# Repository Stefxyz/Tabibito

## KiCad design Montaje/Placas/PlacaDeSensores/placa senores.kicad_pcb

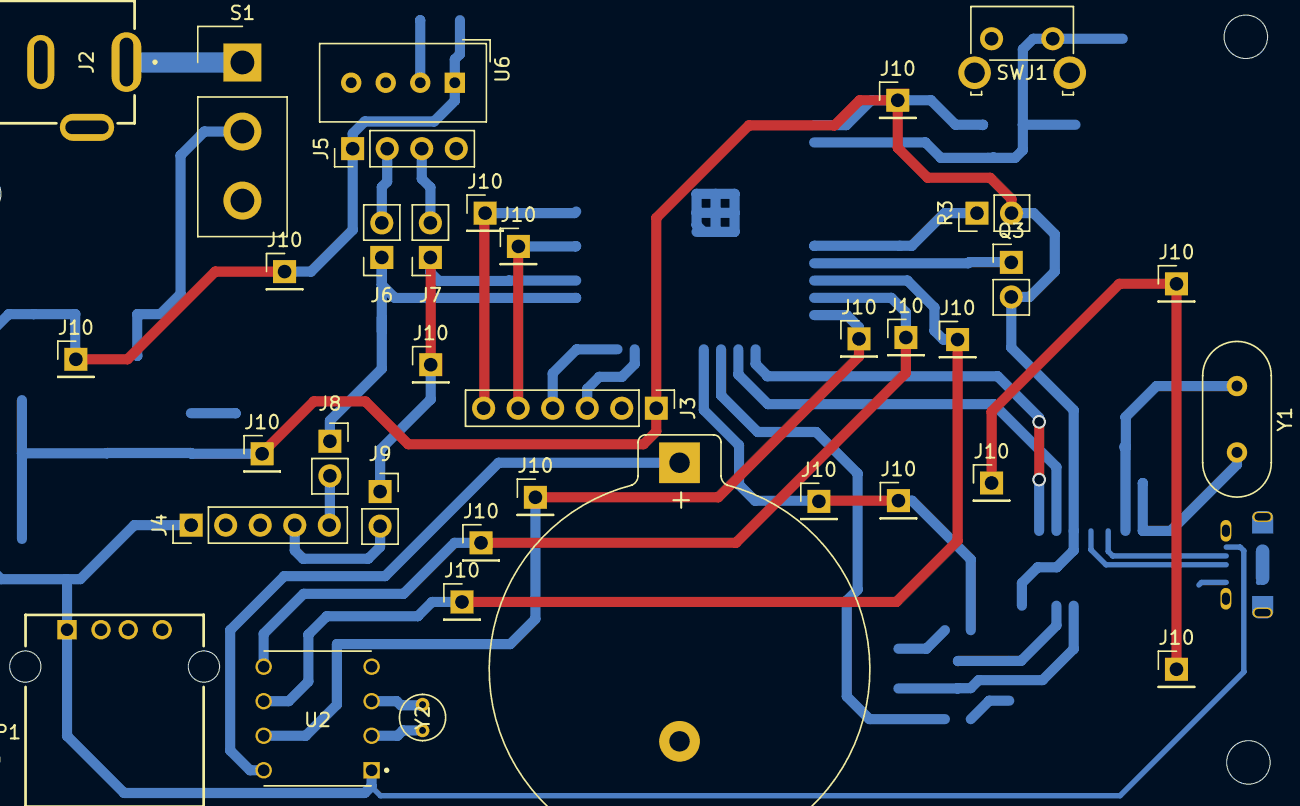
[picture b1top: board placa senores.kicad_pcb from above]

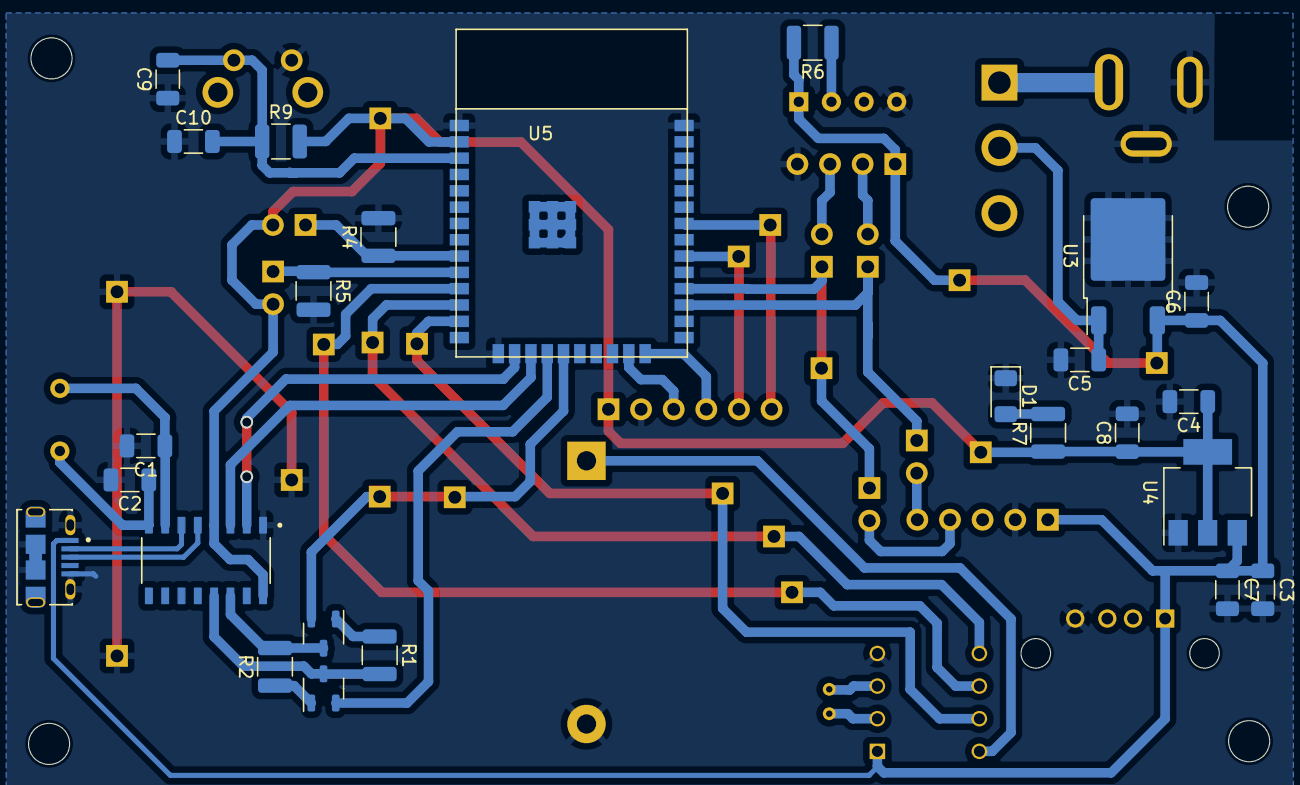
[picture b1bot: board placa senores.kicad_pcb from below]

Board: 2 copper layers, 65 parts (25 on the bottom side), 39 nets.

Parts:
BT1: Pila; BatteryHolder_Keystone_105_1x2430
C1, C2: 22n; C_1206_3216Metric
C3: 0,1uF; C_1206_3216Metric
C4: 10uF; C_1206_3216Metric
C5, C6, C7, C8: 10u; C_1206_3216Metric
C9, C10: 0.1u; C_1206_3216Metric
D1: LED; LED_1206_3216Metric
H1, H2, H3, H4: MountingHole; MountingHole_3.2mm_M3
J1: 10118194-0001LF; AMPHENOL_10118194-0001LF
J2: DCJ200-10-A-XX-K_REVA; GCT_DCJ200-10-A-XX-K_REVA
J3: bmp280; PinHeader_1x06_P2.54mm_Vertical
J4: Screw_Terminal_01x05; PinHeader_1x05_P2.54mm_Vertical
J5: Screw_Terminal_01x04; PinHeader_1x04_P2.54mm_Vertical
J6, J7, J8, J9: Screw_Terminal_01x02; PinSocket_1x02_P2.54mm_Vertical
J10, J10#2, J10#3, J10#4, J10#5, J10#6, J10#7, J10#8, J10#9, J10#10, J10#11, J10#12, J10#13, J10#14, J10#15, J10#16, J10#17, J10#18: Screw_Terminal_01x01; PinHeader_1x01_P2.54mm_Vertical
P1: USB-A1HSW6; OST_USB-A1HSW6
Q1, Q2: BC847; SOT-23-3
Q3: Fototransistor; PinHeader_1x02_P2.54mm_Vertical
R1, R2: 10k; R_1210_3225Metric
R3: LDR07; PinHeader_1x02_P2.54mm_Vertical
R4: 5,6K; R_1210_3225Metric
R5: 1M; R_1210_3225Metric
R6: 4,7K; R_1210_3225Metric
R7: 330; R_1210_3225Metric
R9: 4.7k; R_1210_3225Metric
S1: RB141C1100; Samtec_HPM-03-05-x-S_Straight_1x03_Pitch5.08mm
SWJ1: SW_MEC_5G; SW_SPST_Omron_B3F-315x_Angled
U1: CH340G; SOIC127P600X180-16N
U2: DS1302; DIP794W47P254L991H457Q8
U3: KA78M05_TO252; TO-252-2
U4: AMS1117; SOT-223-3_TabPin2
U5: ESP32-WROOM-32E
U6: DHT11; Aosong_DHT11_5.5x12.0_P2.54mm
Y1: Crystal; Crystal_HC49-4H_Vertical
Y2: Crystal; Crystal_C38-LF_D3.0mm_L8.0mm_Vertical

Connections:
+3V3: C4.1, C8.1, J3.1, J10#6.1, J10#17.1, Q3.2 (E), R3.2, R7.1, R9.2, U1.4 (V3), U1.16 (VCC), U4.2 (VO), U5.2 (VDD)
+5V: C3.1, C6.1, C7.1, J1.1, J4.1, J5.1, J10#11.1, J10#16.1, P1.1 (VBUS), R6.2, U2.1 (VCC), U3.3 (VO), U4.3 (VI), U6.1 (VCC)
/+D: J1.3, U1.5 (UD+)
/-D: J1.2, U1.6 (UD-)
/ADC_LDR: R3.1, R4.1, U5.9 (IO33)
/ADC_PD: Q3.1 (C), R5.1, U5.10 (IO25)
/CLK: J10#2.1, J10#12.1, U2.7 (SCLK), U5.13 (IO14)
/CSB: J3.5, J10#8.1, U5.30 (IO18)
/DTR: Q2.3 (E), R1.2, U1.13 (~DTR)
/Data: J10.1, J10#7.1, U2.6 (I/O), U5.11 (IO26)
/EN: C9.2, C10.2, R9.1, SWJ1.2 (B), U5.3 (EN)
/EN 1: J10#9.1, J10#15.1, Q1.2 (C), U5.19 (NC@19)
/GPIO_DHT22: R6.1, U6.2 (IO)
/ID0: Q2.2 (C), U5.18 (NC@18)
/RESET: J10#10.1, J10#13.1, U2.5 (CE), U5.12 (IO27)
/RST: Q1.3 (E), R2.2, U1.14 (~RTS)
/RX0: J4.4, J9.2
/RX01: J5.3, J7.2
/RX pin: J7.1, J9.1, J10#5.1, U5.28 (IO17)
/Rx: U1.3 (RXD), U5.17 (NC@17)
/SCL: J3.3, U5.23 (IO15)
/SDA: J3.4, U5.24 (IO2)
/SDO: J3.6, J10#3.1, U5.32 (NC@32)
/TX0: J4.5, J8.2
/TX01: J5.2, J6.2
/TX pin: J6.1, J8.1, U5.27 (IO16)
/Tx: U1.2 (TXD), U5.16 (IO13)
/Vin: J2.1, S1.1
/Vpila: BT1.1 (+), U2.8 (VBAT)
/XI: C1.1, U1.7 (XI), Y1.1
/XO: C2.1, U1.8 (XO), Y1.2
GND: BT1.2 (-), C1.2, C2.2, C3.2, C4.2, C5.2, C6.2, C7.2, C8.2, C9.1, C10.1, D1.1 (K), J1.5, J1.S1 (SHIELD), J1.S2 (SHIELD), J1.S4 (SHIELD), J1.S5 (SHIELD), J2.2, J2.3, J3.2, J4.2, J5.4, J10#4.1, J10#14.1, J10#18.1, P1.4 (GND), R4.2, R5.2, SWJ1.1 (A), U1.1 (GND), U2.4 (GND), U3.2 (GND), U4.1 (ADJ), U5.1 (GND@1), U5.15 (GND@15), U5.38 (GND@38), U6.4 (GND)
unnamed: D1.2 (A), R7.2
unnamed: Q1.1 (B), R1.1
unnamed: Q2.1 (B), R2.1
unnamed: U2.2 (X1), Y2.2
unnamed: U2.3 (X2), Y2.1
unnamed: U5.GND@39 (THERMAL@39), U5.GND@40 (THERMAL@39), U5.GND@41 (THERMAL@39), U5.GND@42 (THERMAL@39), U5.GND@43 (THERMAL@39), U5.GND@44 (THERMAL@39), U5.GND@45 (THERMAL@39), U5.GND@46 (THERMAL@39), U5.GND@47 (THERMAL@39)
VCC: C5.1, S1.2, U3.1 (VI)

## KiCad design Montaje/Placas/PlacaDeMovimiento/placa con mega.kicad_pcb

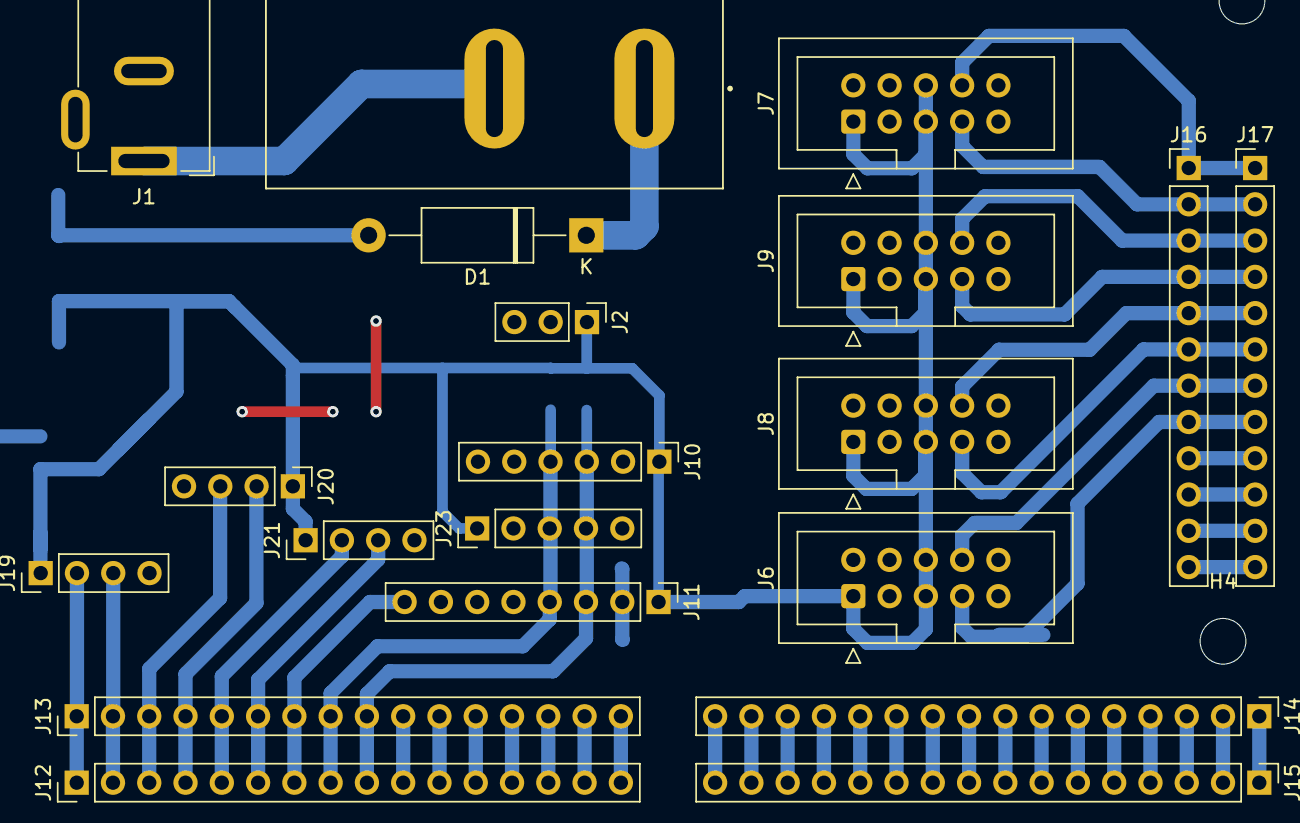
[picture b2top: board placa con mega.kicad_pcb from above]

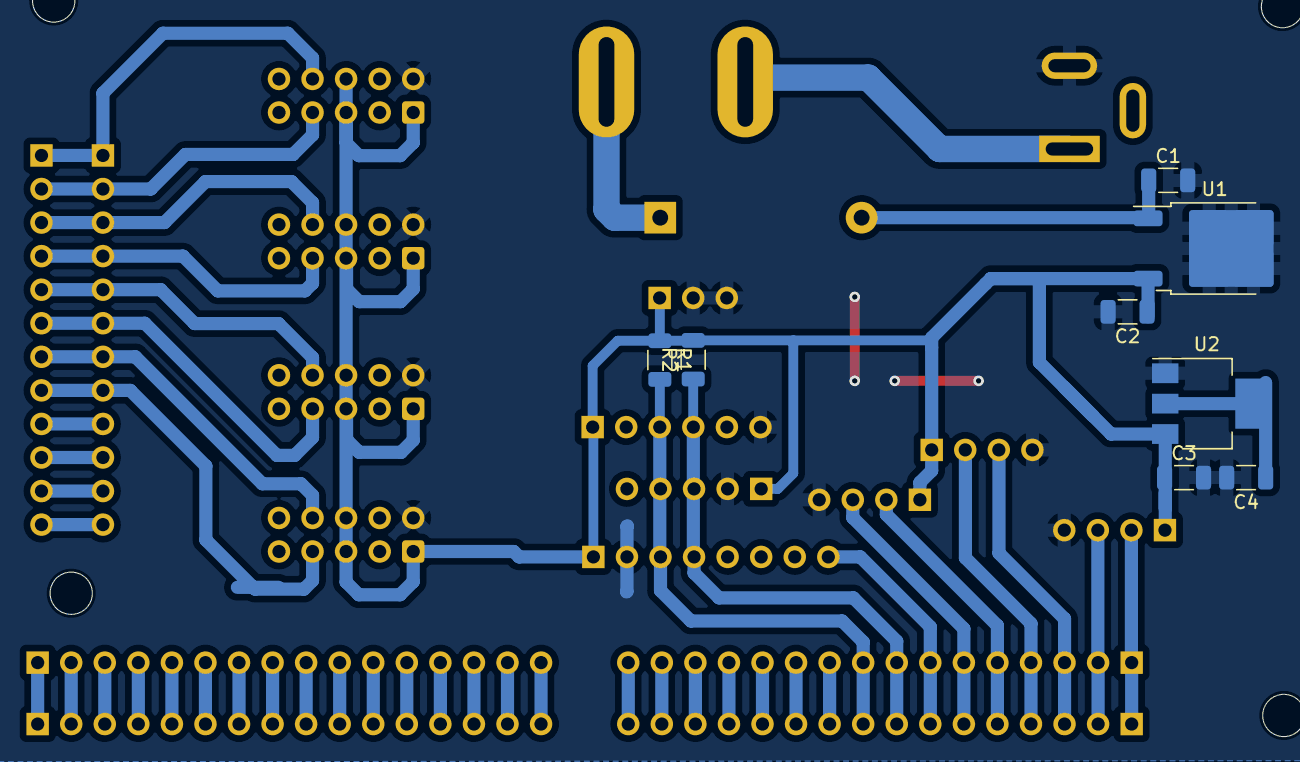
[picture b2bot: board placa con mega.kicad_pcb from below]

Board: 2 copper layers, 32 parts (8 on the bottom side), 50 nets.

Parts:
C1: 0,33uF; C_1206_3216Metric
C2: 0,1uF; C_1206_3216Metric
C3, C4: 10u; C_1206_3216Metric
D1: DIODE; D_DO-15_P15.24mm_Horizontal
H1, H2, H3, H4: MountingHole; MountingHole_3.2mm_M3
J1: Jack-DC; BarrelJack_GCT_DCJ200-10-A_Horizontal
J2: Screw_Terminal_01x03; PinHeader_1x03_P2.54mm_Vertical
J6: motor 1; IDC-Header_2x05_P2.54mm_Vertical
J7: motor 2; IDC-Header_2x05_P2.54mm_Vertical
J8: motor 4; IDC-Header_2x05_P2.54mm_Vertical
J9: motor 3; IDC-Header_2x05_P2.54mm_Vertical
J10: Screw_Terminal_01x06; PinHeader_1x06_P2.54mm_Vertical
J11: Screw_Terminal_01x08; PinHeader_1x08_P2.54mm_Vertical
J12: Digitales; PinHeader_1x16_P2.54mm_Vertical
J13, J14: Screw_Terminal_01x16; PinHeader_1x16_P2.54mm_Vertical
J15: Analogicos; PinHeader_1x16_P2.54mm_Vertical
J16: PWM; PinHeader_1x12_P2.54mm_Vertical
J17: Screw_Terminal_01x12; PinHeader_1x12_P2.54mm_Vertical
J19, J20, J21: Screw_Terminal_01x04; PinHeader_1x04_P2.54mm_Vertical
J23: Screw_Terminal_01x05; PinHeader_1x05_P2.54mm_Vertical
R1, R2: 10K; R_1206_3216Metric
SW1: SW_SPDT; SW_RB141C1100
U1: L7805; TO-252-2
U2: AMS1117; SOT-223-3_TabPin2

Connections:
+3V3: C4.1, U2.2 (VO)
+5V: C2.1, C3.1, J2.1, J6.1, J6.5, J6.6, J7.1, J7.5, J7.6, J8.1, J8.5, J8.6, J9.1, J9.5, J9.6, J10.1, J11.1, J19.1, J20.1, J21.1, J23.1, R1.1, R2.2, U1.3 (OUT), U2.3 (VI)
+12V: C1.1, D1.2 (K), U1.1 (IN)
/ECHO: J12.2, J13.2, J19.3
/ECHO1: J12.3, J13.3, J20.3
/ECHO2: J12.6, J13.6, J21.3
/INT: J11.8, J12.7, J13.7
/PWM_M1_L: J7.8, J16.1, J17.1
/PWM_M1_R: J7.7, J16.2, J17.2
/PWM_M2_L: J9.8, J16.3, J17.3
/PWM_M2_R: J9.7, J16.4, J17.4
/PWM_M3_L: J8.8, J16.5, J17.5
/PWM_M3_R: J8.7, J16.6, J17.6
/PWM_M4_L: J6.8, J16.7, J17.7
/PWM_M4_R: J6.7, J16.8, J17.8
/SCL_1: J10.4, J11.4, J12.8, J13.8, J23.3, R2.1
/SDA_1: J10.3, J11.3, J12.9, J13.9, J23.4, R1.2
/TRIG: J12.1, J13.1, J19.2
/TRIG1: J12.4, J13.4, J20.2
/TRIG2: J12.5, J13.5, J21.2
GND: C1.2, C2.2, C3.2, C4.2, J1.2, J2.2, J2.3, J6.2, J7.2, J8.2, J9.2, J10.6, J11.2, J19.4, J20.4, J21.4, J23.2, U1.2 (GND), U2.1 (ADJ)
unnamed: D1.1 (A), SW1.1 (A)
unnamed: J12.10, J13.10
unnamed: J12.11, J13.11
unnamed: J12.12, J13.12
unnamed: J12.13, J13.13
unnamed: J12.14, J13.14
unnamed: J12.15, J13.15
unnamed: J12.16, J13.16
unnamed: J14.1, J15.1
unnamed: J14.2, J15.2
unnamed: J14.3, J15.3
unnamed: J14.4, J15.4
unnamed: J14.5, J15.5
unnamed: J14.6, J15.6
unnamed: J14.7, J15.7
unnamed: J14.8, J15.8
unnamed: J14.9, J15.9
unnamed: J14.10, J15.10
unnamed: J14.11, J15.11
unnamed: J14.12, J15.12
unnamed: J14.13, J15.13
unnamed: J14.14, J15.14
unnamed: J14.15, J15.15
unnamed: J14.16, J15.16
unnamed: J16.9, J17.9
unnamed: J16.10, J17.10
unnamed: J16.11, J17.11
unnamed: J16.12, J17.12
unnamed: J1.1, SW1.2 (B)
